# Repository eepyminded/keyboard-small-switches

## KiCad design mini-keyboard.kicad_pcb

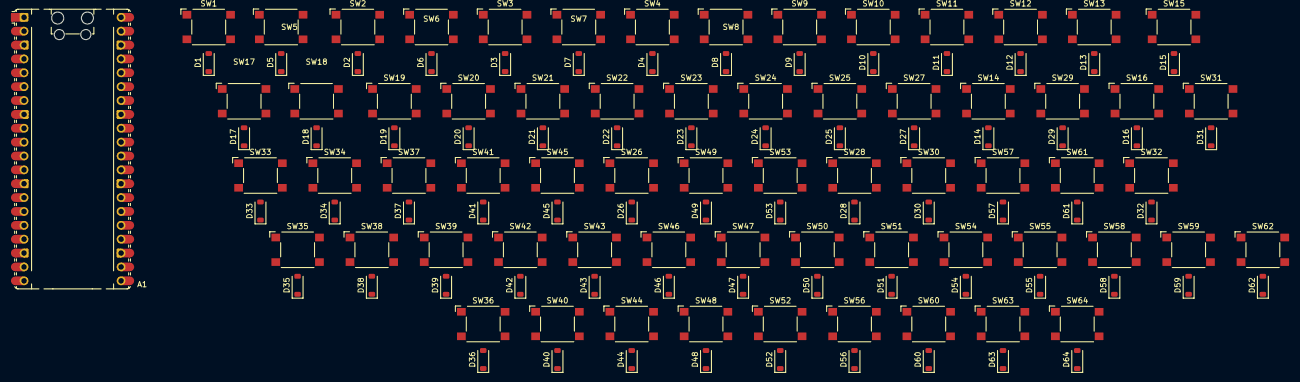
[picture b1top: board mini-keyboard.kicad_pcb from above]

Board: 2 copper layers, 129 parts (0 on the bottom side), 81 nets, no tracks yet.

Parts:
A1: RaspberryPi_Pico; RaspberryPi_Pico_Common_Unspecified
D1, D2, D3, D4, D5, D6, D7, D8, D9, D10, D11, D12, D13, D14, D15, D16, D17, D18, D19, D20, D21, D22, D23, D24, D25, D26, D27, D28, D29, D30, D31, D32, D33, D34, D35, D36, D37, D38, D39, D40, D41, D42, D43, D44, D45, D46, D47, D48, D49, D50, D51, D52, D53, D54, D55, D56, D57, D58, D59, D60, D61, D62, D63, D64: 1N4148; D_SOD-123
SW1, SW2, SW3, SW4, SW5, SW6, SW7, SW8, SW9, SW10, SW11, SW12, SW13, SW14, SW15, SW16, SW17, SW18, SW19, SW20, SW21, SW22, SW23, SW24, SW25, SW26, SW27, SW28, SW29, SW30, SW31, SW32, SW33, SW34, SW35, SW36, SW37, SW38, SW39, SW40, SW41, SW42, SW43, SW44, SW45, SW46, SW47, SW48, SW49, SW50, SW51, SW52, SW53, SW54, SW55, SW56, SW57, SW58, SW59, SW60, SW61, SW62, SW63, SW64: SW_Push_45deg; SW_SPST_Omron_B3FS-100xP

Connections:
/Column 0: A1.1 (GPIO0), SW1.1, SW5.1, SW17.1, SW18.1, SW33.1, SW34.1, SW35.1, SW36.1
/Column 1: A1.2 (GPIO1), SW2.1, SW6.1, SW19.1, SW20.1, SW37.1, SW38.1, SW39.1, SW40.1
/Column 2: A1.4 (GPIO2), SW3.1, SW7.1, SW21.1, SW22.1, SW41.1, SW42.1, SW43.1, SW44.1
/Column 3: A1.5 (GPIO3), SW4.1, SW8.1, SW23.1, SW24.1, SW45.1, SW46.1, SW47.1, SW48.1
/Column 4: A1.6 (GPIO4), SW9.1, SW10.1, SW25.1, SW26.1, SW49.1, SW50.1, SW51.1, SW52.1
/Column 5: A1.7 (GPIO5), SW11.1, SW12.1, SW27.1, SW28.1, SW53.1, SW54.1, SW55.1, SW56.1
/Column 6: A1.9 (GPIO6), SW13.1, SW14.1, SW29.1, SW30.1, SW57.1, SW58.1, SW59.1, SW60.1
/Column 7: A1.10 (GPIO7), SW15.1, SW16.1, SW31.1, SW32.1, SW61.1, SW62.1, SW63.1, SW64.1
/Row 0: A1.11 (GPIO8), D1.1 (K), D2.1 (K), D3.1 (K), D4.1 (K), D9.1 (K), D11.1 (K), D13.1 (K), D15.1 (K)
/Row 1: A1.12 (GPIO9), D5.1 (K), D6.1 (K), D7.1 (K), D8.1 (K), D10.1 (K), D12.1 (K), D14.1 (K), D16.1 (K)
/Row 2: A1.14 (GPIO10), D17.1 (K), D19.1 (K), D21.1 (K), D23.1 (K), D25.1 (K), D27.1 (K), D29.1 (K), D31.1 (K)
/Row 3: A1.15 (GPIO11), D18.1 (K), D20.1 (K), D22.1 (K), D24.1 (K), D26.1 (K), D28.1 (K), D30.1 (K), D32.1 (K)
/Row 4: A1.16 (GPIO12), D33.1 (K), D37.1 (K), D41.1 (K), D45.1 (K), D49.1 (K), D53.1 (K), D57.1 (K), D61.1 (K)
/Row 5: A1.17 (GPIO13), D34.1 (K), D38.1 (K), D42.1 (K), D46.1 (K), D50.1 (K), D54.1 (K), D58.1 (K), D62.1 (K)
/Row 6: A1.19 (GPIO14), D35.1 (K), D39.1 (K), D43.1 (K), D47.1 (K), D51.1 (K), D55.1 (K), D59.1 (K), D63.1 (K)
/Row 7: A1.20 (GPIO15), D36.1 (K), D40.1 (K), D44.1 (K), D48.1 (K), D52.1 (K), D56.1 (K), D60.1 (K), D64.1 (K)
unnamed: A1.3 (GND), A1.8 (GND), A1.13 (GND), A1.18 (GND), A1.23 (GND), A1.28 (GND), A1.38 (GND)
unnamed: D1.2 (A), SW1.2
unnamed: D2.2 (A), SW2.2
unnamed: D3.2 (A), SW3.2
unnamed: D4.2 (A), SW4.2
unnamed: D5.2 (A), SW5.2
unnamed: D6.2 (A), SW6.2
unnamed: D7.2 (A), SW7.2
unnamed: D8.2 (A), SW8.2
unnamed: D9.2 (A), SW9.2
unnamed: D10.2 (A), SW10.2
unnamed: D11.2 (A), SW11.2
unnamed: D12.2 (A), SW12.2
unnamed: D13.2 (A), SW13.2
unnamed: D14.2 (A), SW14.2
unnamed: D15.2 (A), SW15.2
unnamed: D16.2 (A), SW16.2
unnamed: D17.2 (A), SW17.2
unnamed: D18.2 (A), SW18.2
unnamed: D19.2 (A), SW19.2
unnamed: D20.2 (A), SW20.2
unnamed: D21.2 (A), SW21.2
unnamed: D22.2 (A), SW22.2
unnamed: D23.2 (A), SW23.2
unnamed: D24.2 (A), SW24.2
unnamed: D25.2 (A), SW25.2
unnamed: D26.2 (A), SW26.2
unnamed: D27.2 (A), SW27.2
unnamed: D28.2 (A), SW28.2
unnamed: D29.2 (A), SW29.2
unnamed: D30.2 (A), SW30.2
unnamed: D31.2 (A), SW31.2
unnamed: D32.2 (A), SW32.2
unnamed: D33.2 (A), SW33.2
unnamed: D34.2 (A), SW34.2
unnamed: D35.2 (A), SW35.2
unnamed: D36.2 (A), SW36.2
unnamed: D37.2 (A), SW37.2
unnamed: D38.2 (A), SW38.2
unnamed: D39.2 (A), SW39.2
unnamed: D40.2 (A), SW40.2
unnamed: D41.2 (A), SW41.2
unnamed: D42.2 (A), SW42.2
unnamed: D43.2 (A), SW43.2
unnamed: D44.2 (A), SW44.2
unnamed: D45.2 (A), SW45.2
unnamed: D46.2 (A), SW46.2
unnamed: D47.2 (A), SW47.2
unnamed: D48.2 (A), SW48.2
unnamed: D49.2 (A), SW49.2
unnamed: D50.2 (A), SW50.2
unnamed: D51.2 (A), SW51.2
unnamed: D52.2 (A), SW52.2
unnamed: D53.2 (A), SW53.2
unnamed: D54.2 (A), SW54.2
unnamed: D55.2 (A), SW55.2
unnamed: D56.2 (A), SW56.2
unnamed: D57.2 (A), SW57.2
unnamed: D58.2 (A), SW58.2
unnamed: D59.2 (A), SW59.2
unnamed: D60.2 (A), SW60.2
unnamed: D61.2 (A), SW61.2
unnamed: D62.2 (A), SW62.2
unnamed: D63.2 (A), SW63.2
unnamed: D64.2 (A), SW64.2
